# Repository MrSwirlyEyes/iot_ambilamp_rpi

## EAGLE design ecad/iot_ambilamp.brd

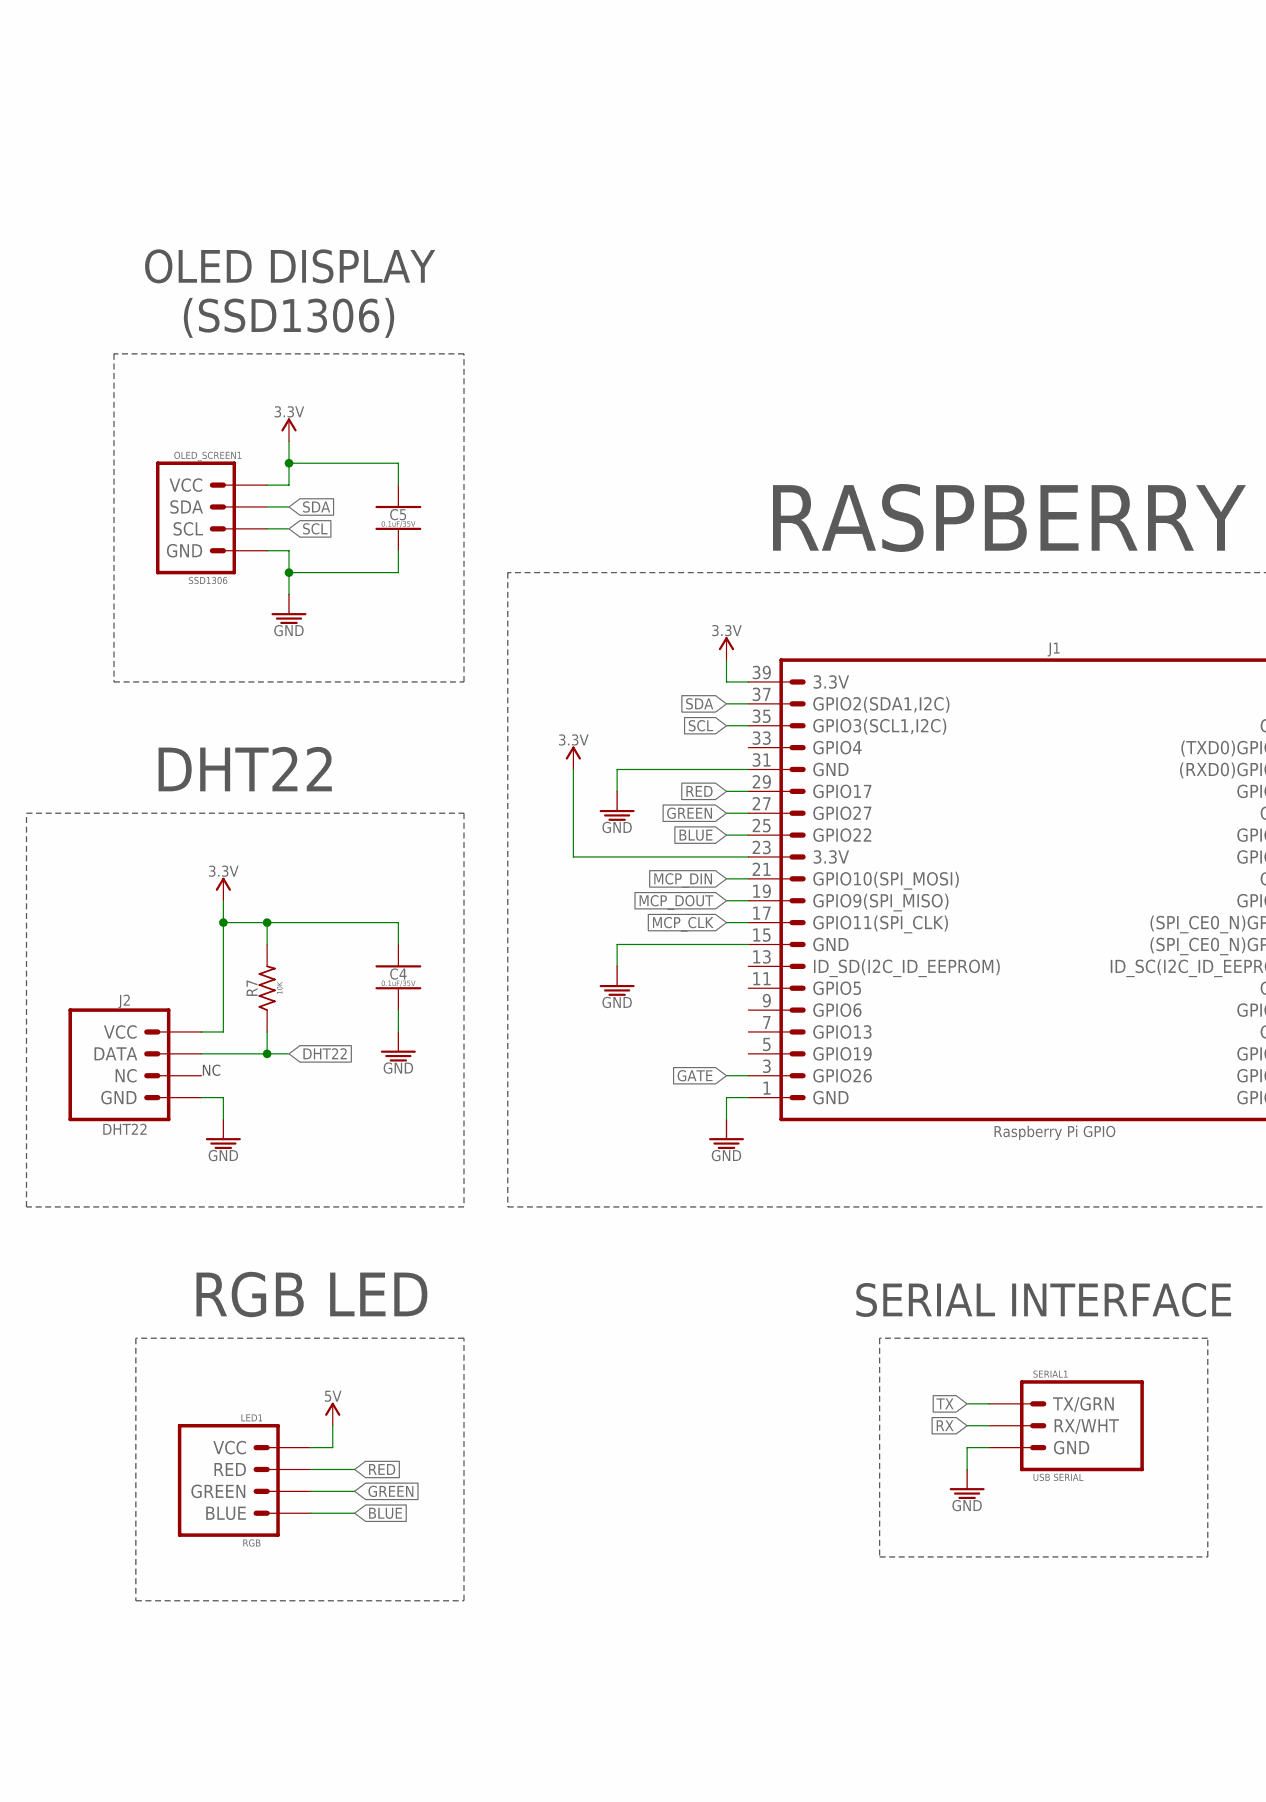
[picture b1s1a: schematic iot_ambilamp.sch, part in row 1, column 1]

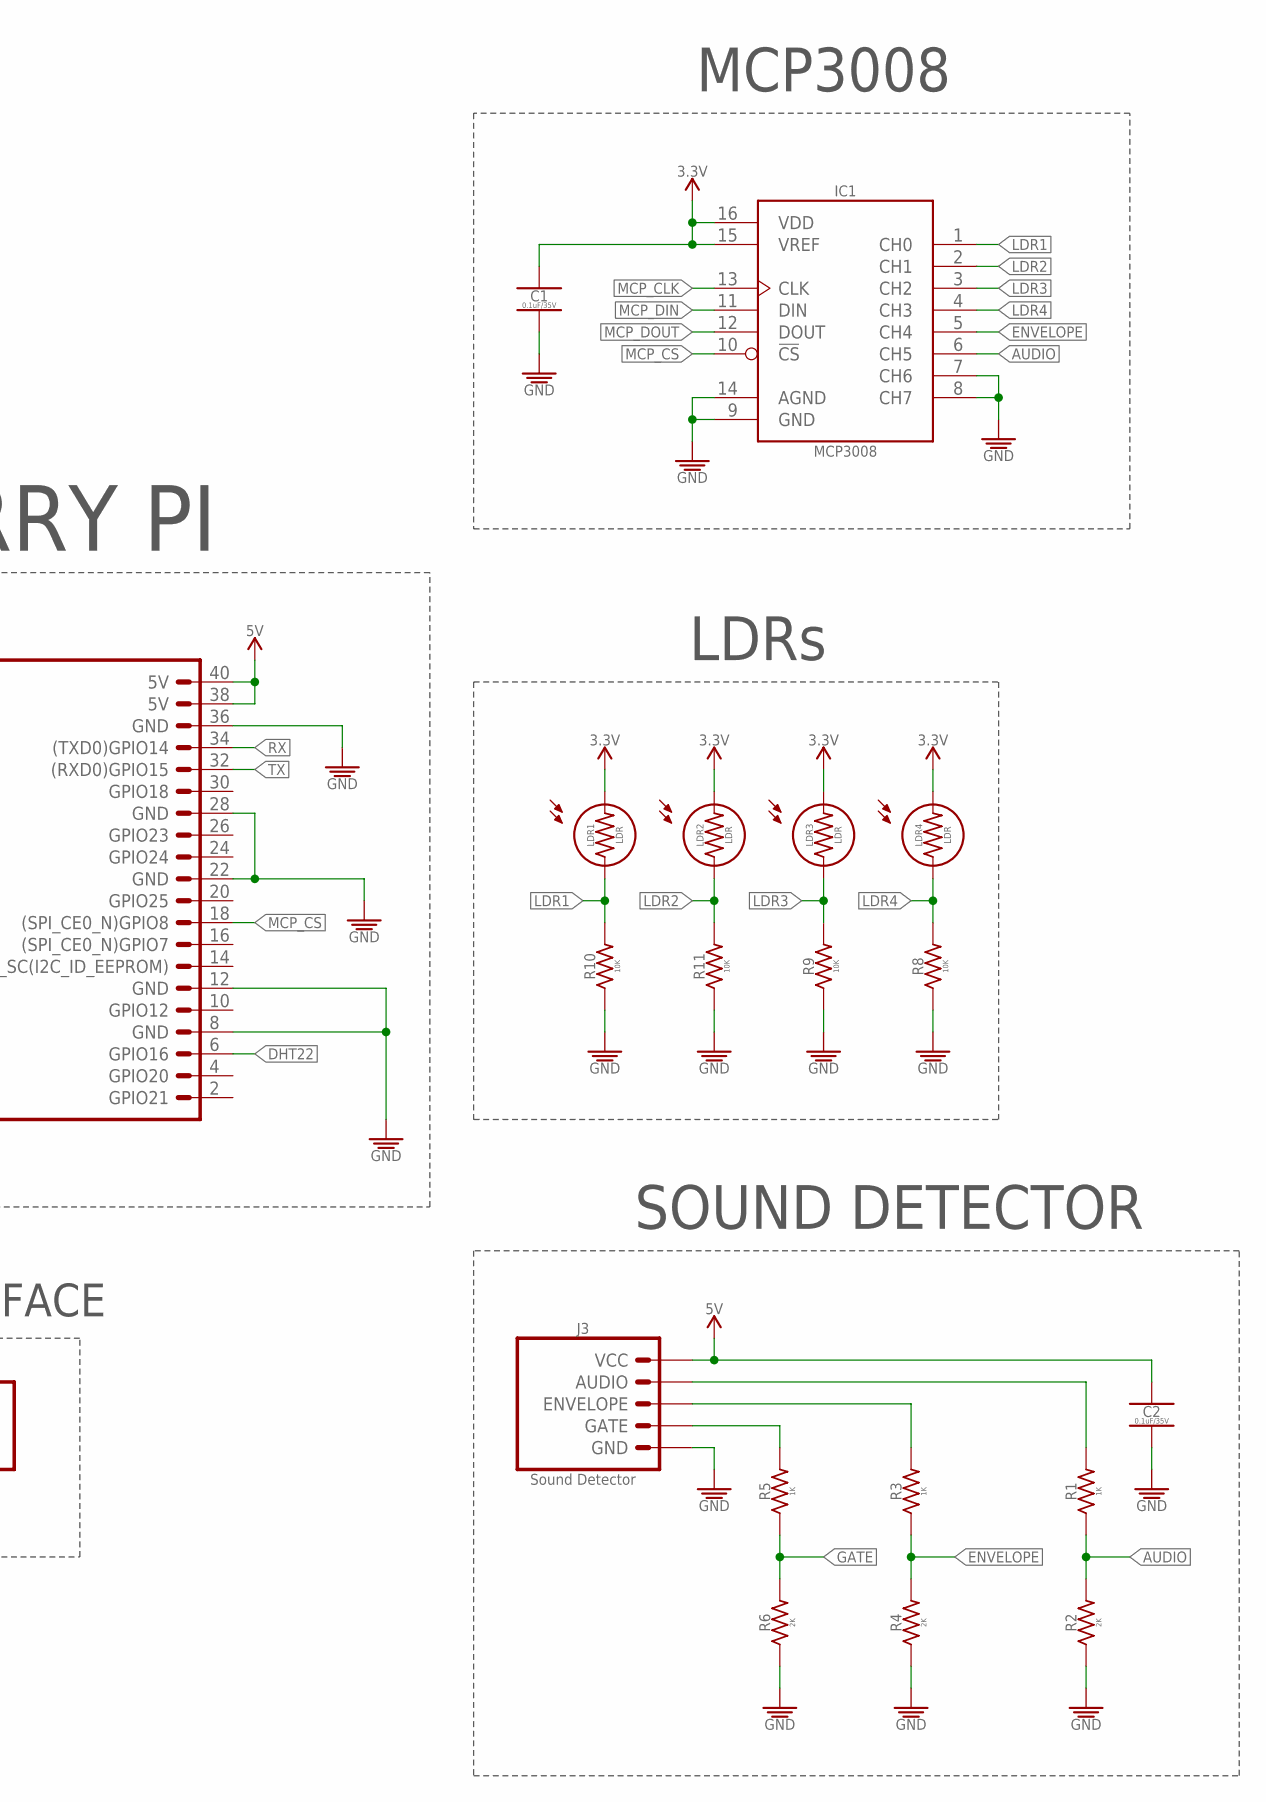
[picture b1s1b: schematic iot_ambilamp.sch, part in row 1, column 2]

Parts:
C1, C2, C4, C5: 0.1uF/35V; CAPC2012X95_SMD-0805
IC1: MCP3008; SOIC127P600X175-16
J1: Raspberry Pi GPIO; HDRVR40W64P254_2X20_5130X500X1350B
J2: DHT22; TEMPERATURE-SENSOR_DHT22
J3: Sound Detector; HDRV5W64P254_1X5_1270X254X838B
LDR1, LDR2, LDR3, LDR4: LDR; PHOTORESISTOR_TALL
LED1: RGB; HDRVR4W75P254_1X4_1066X254X850B
OLED_SCREEN1: SSD1306; HDRV4W64P254_1X4_1016X254X838B
R1, R3, R5: 1K; RESC2012X60_SMD-0805
R2, R4, R6: 2K; RESC2012X60_SMD-0805
R7, R8, R9, R10, R11: 10K; RESC2012X60_SMD-0805
SERIAL1: USB SERIAL; HDRV3W64P254_1X3_762X254X838B_USB-SERIAL-CABLE

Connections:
3.3V: C1.1, C4.1, C5.1, IC1.15 (VREF), IC1.16 (VDD), J1.23 (3.3V), J1.39 (3.3V), J2.VCC, LDR1.P$2 (2), LDR2.P$2 (2), LDR3.P$2 (2), LDR4.P$2 (2), OLED_SCREEN1.VCC, R7.2
5V: C2.1, J1.38 (5V), J1.40 (5V), J3.VCC, LED1.VCC
AUDIO: IC1.6 (CH5), R1.1, R2.2
BLUE: J1.25 (GPIO22), LED1.BLUE
DHT22: J1.6 (GPIO16), J2.DATA, R7.1
ENVELOPE: IC1.5 (CH4), R3.1, R4.2
GATE: J1.3 (GPIO26), R5.1, R6.2
GND: C1.2, C2.2, C4.2, C5.2, IC1.7 (CH6), IC1.8 (CH7), IC1.9 (GND), IC1.14 (AGND), J1.1 (GND), J1.8 (GND), J1.12 (GND), J1.15 (GND), J1.22 (GND), J1.28 (GND), J1.31 (GND), J1.36 (GND), J2.GND, J3.GND, OLED_SCREEN1.GND, R2.1, R4.1, R6.1, R8.1, R9.1, R10.1, R11.1, SERIAL1.GND
GREEN: J1.27 (GPIO27), LED1.GREEN
LDR1: IC1.1 (CH0), LDR1.P$1 (1), R10.2
LDR2: IC1.2 (CH1), LDR2.P$1 (1), R11.2
LDR3: IC1.3 (CH2), LDR3.P$1 (1), R9.2
LDR4: IC1.4 (CH3), LDR4.P$1 (1), R8.2
MCP_CLK: IC1.13 (CLK), J1.17 (GPIO11(SPI_CLK))
MCP_CS: IC1.10 (!CS), J1.18 ((SPI_CE0_N)GPIO8)
MCP_DIN: IC1.11 (DIN), J1.21 (GPIO10(SPI_MOSI))
MCP_DOUT: IC1.12 (DOUT), J1.19 (GPIO9(SPI_MISO))
unnamed: J3.AUDIO, R1.2
unnamed: J3.ENVELOPE, R3.2
unnamed: J3.GATE, R5.2
RED: J1.29 (GPIO17), LED1.RED
RX: J1.34 ((TXD0)GPIO14), SERIAL1.RX/WHT
SCL: J1.35 (GPIO3(SCL1,I2C)), OLED_SCREEN1.SCL
SDA: J1.37 (GPIO2(SDA1,I2C)), OLED_SCREEN1.SDA
TX: J1.32 ((RXD0)GPIO15), SERIAL1.TX/GRN

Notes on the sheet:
RASPBERRY PI
DHT22
OLED DISPLAY (SSD1306)
SERIAL INTERFACE
MCP3008
LDRs
RGB LED
SOUND DETECTOR

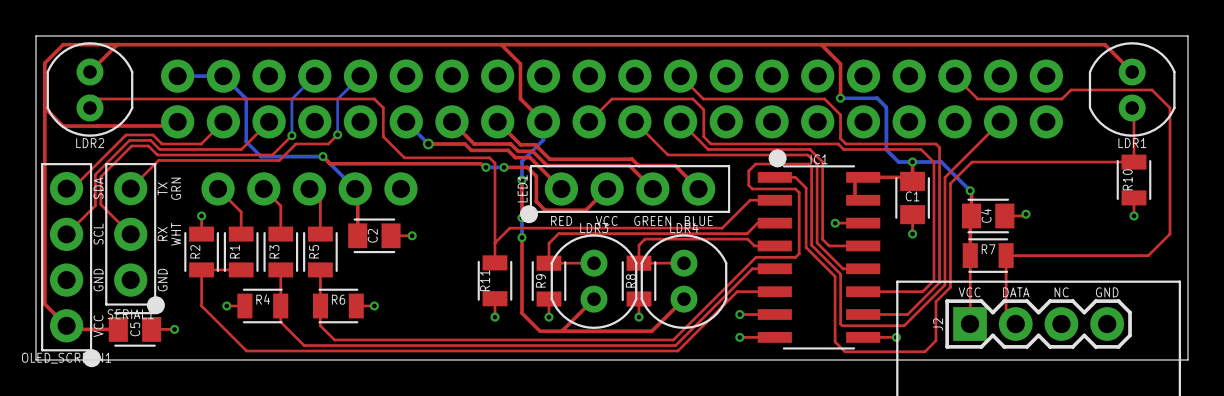
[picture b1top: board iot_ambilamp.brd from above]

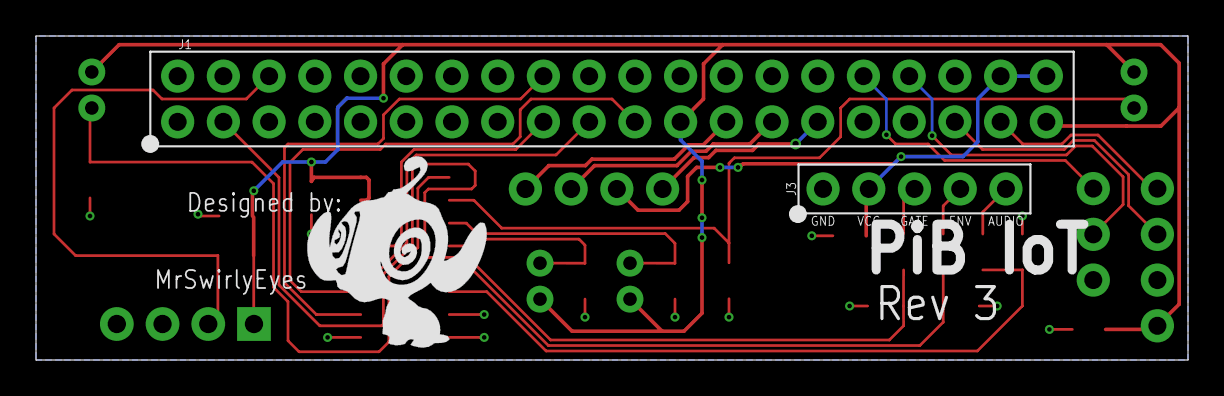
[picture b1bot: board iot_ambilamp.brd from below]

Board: 2 copper layers, 64.0 x 18.0 mm, 27 parts (3 on the bottom side), 25 nets.

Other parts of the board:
U$2: MRSWIRLYEYES-LOGO

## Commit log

2019-02-08 Initialize intro to iot ambilamp repo.
2019-09-28 Update board.
2022-12-07 Bump qs and express in /code/node_examples/2_test_installing_express
    Bumps [qs](https://github.com/ljharb/qs) to 6.11.0 and updates ancestor dependency [express](https://github.com/expressjs/express). These dependencies need to be updated together.
    Updates `qs` from 6.5.1 to 6.11.0
    - [Release notes](https://github.com/ljharb/qs/releases)
    - [Changelog](https://github.com/ljharb/qs/blob/main/CHANGELOG.md)
    - [Commits](https://github.com/ljharb/qs/compare/v6.5.1...v6.11.0)
    Updates `express` from 4.16.2 to 4.18.2
2022-12-07 Bump express in /code/node_examples/2_test_installing_express
    Bumps [express](https://github.com/expressjs/express) from 4.16.2 to 4.17.3.
    - [Release notes](https://github.com/expressjs/express/releases)
    - [Changelog](https://github.com/expressjs/express/blob/master/History.md)
    - [Commits](https://github.com/expressjs/express/compare/4.16.2...4.17.3)
    ---
    updated-dependencies:
